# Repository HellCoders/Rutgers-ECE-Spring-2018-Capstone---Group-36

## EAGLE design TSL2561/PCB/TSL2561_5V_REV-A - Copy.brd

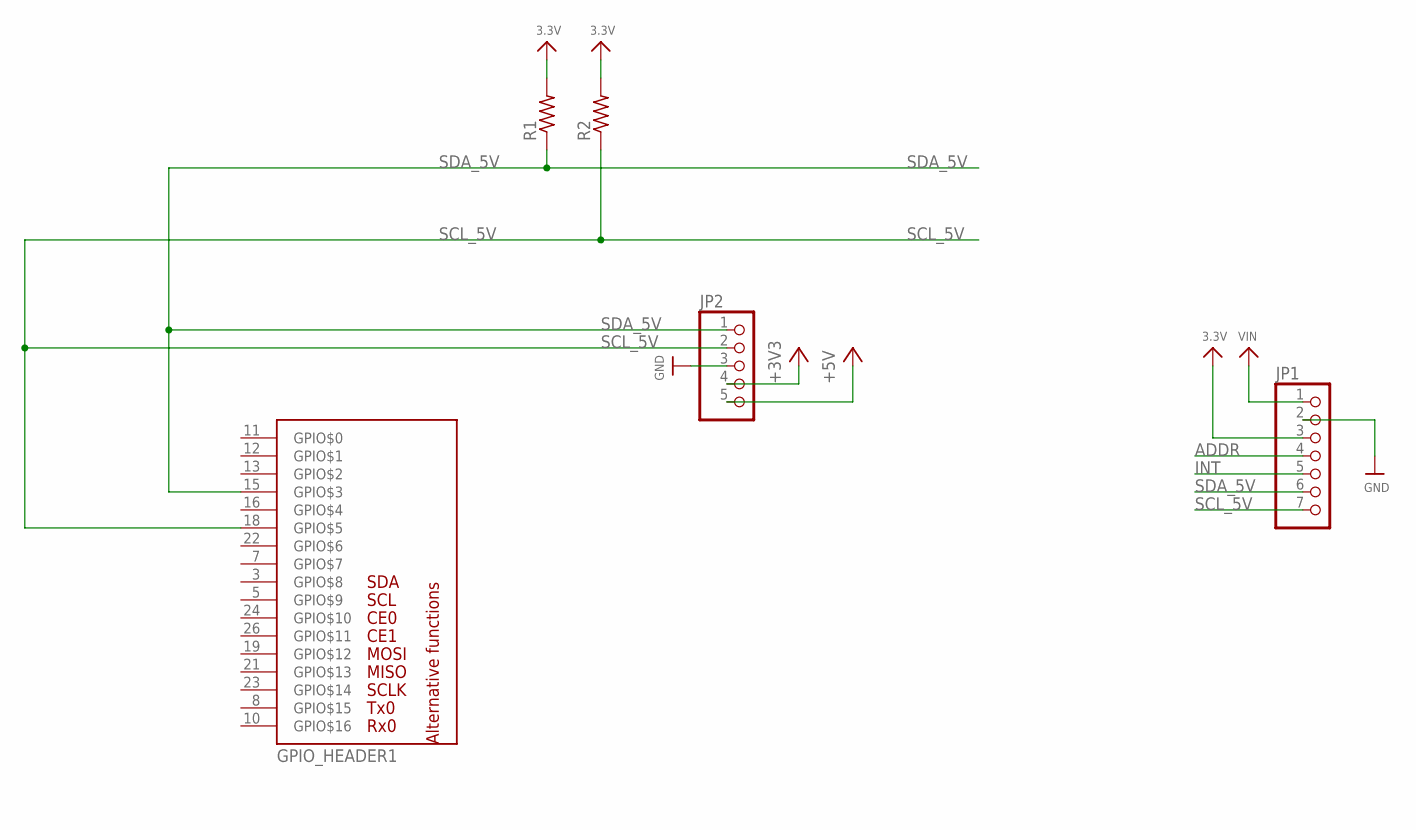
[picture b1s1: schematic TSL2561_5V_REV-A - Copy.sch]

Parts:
GPIO_HEADER1: RPI_GPIO_HEADER; 2X13
JP1: HEADER-1X7THICKER; 1X07_ROUND_76
JP2: HEADER-1X570MIL; 1X05_ROUND_70
R1, R2: R-US_0204/2V; 0204V

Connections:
3.3V: JP1.3, R1.2, R2.2
+3V3: GPIO_HEADER1.1 (+3V3), GPIO_HEADER1.17 (+3V3), JP2.4
+5V: GPIO_HEADER1.2 (+5V), GPIO_HEADER1.4 (+5V)
ADDR: JP1.4
GND: GPIO_HEADER1.6 (GND), GPIO_HEADER1.9 (GND), GPIO_HEADER1.14 (GND), GPIO_HEADER1.20 (GND), GPIO_HEADER1.25 (GND), JP1.2, JP2.3
INT: JP1.5
SCL_5V: GPIO_HEADER1.18 (GPIO$5), JP1.7, JP2.2, R2.1
SDA_5V: GPIO_HEADER1.15 (GPIO$3), JP1.6, JP2.1, R1.1
VIN: JP1.1, JP2.5

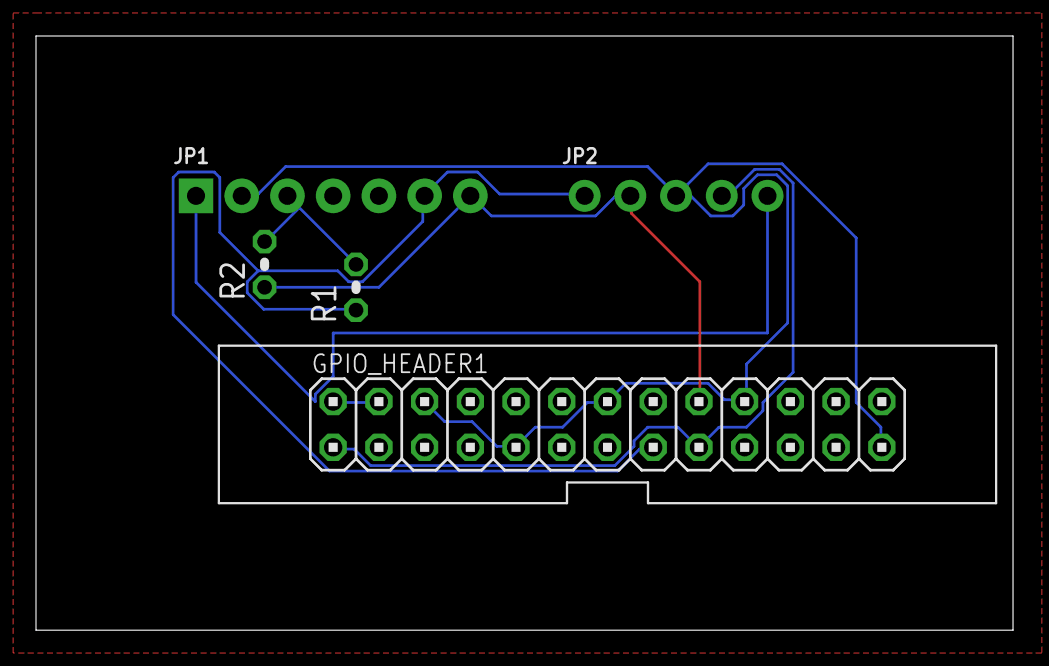
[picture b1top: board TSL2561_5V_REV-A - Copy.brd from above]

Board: 2 copper layers, 54.3 x 33.0 mm, 5 parts (0 on the bottom side), 7 nets.

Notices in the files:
parts and their libraries:
microbuilder: This work is placed in the public domain, and may be freely used for commercial and non-commercial work with the following conditions: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
